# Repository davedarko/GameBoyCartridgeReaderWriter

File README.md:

# GameBoyCartridgeReaderWriter

it's currently a bit unsorted, but here you can find some more information on this project https://hackaday.io/project/16188/

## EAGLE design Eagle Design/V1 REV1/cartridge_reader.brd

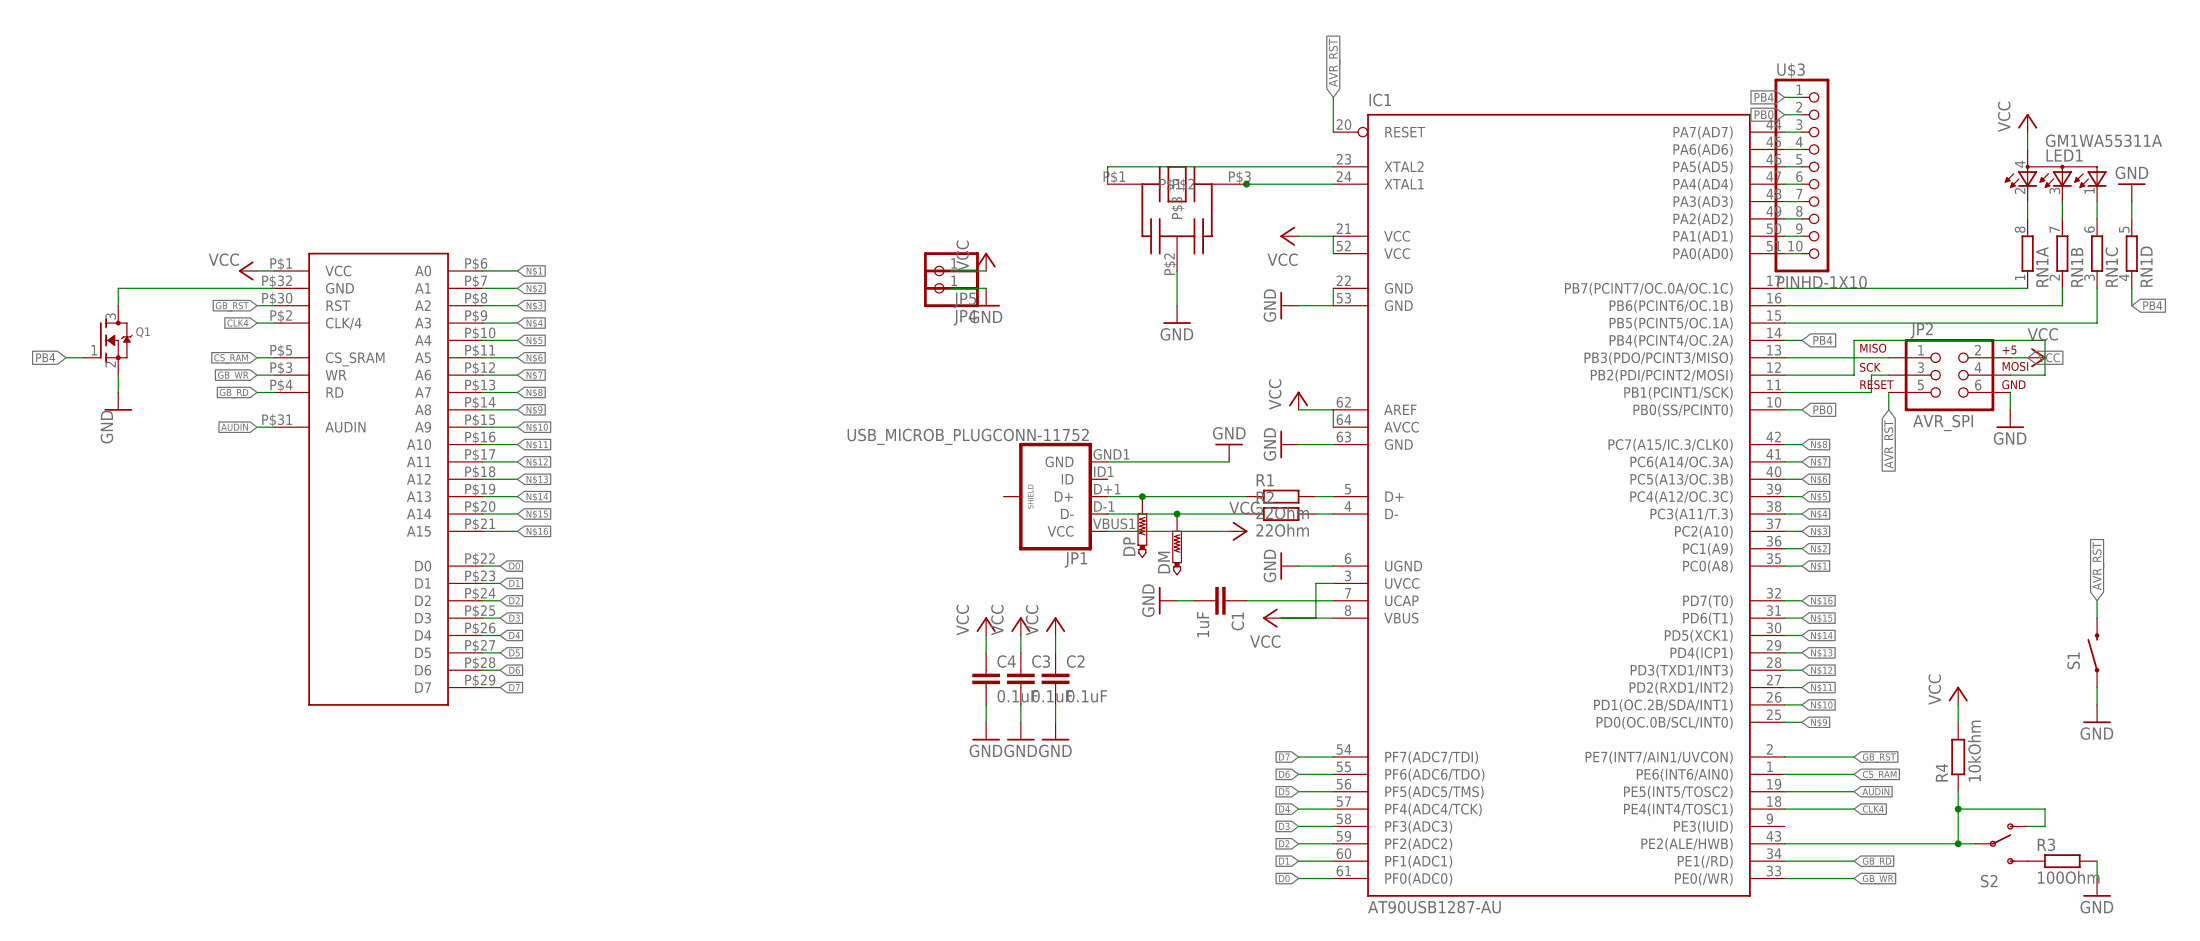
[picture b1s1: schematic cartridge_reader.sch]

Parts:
C1: 1uF; C0805K
C2, C3, C4: 0.1uF; C0805K
DM: PTR1TP18R; TP18R
DP: PTR1TP18R; TP18R
IC1: AT90USB1287-AU; TQFP64
JP1: USB_MICROB_PLUGCONN-11752; USB-B-MICRO-SMD_V03
JP2: AVR_SPI; 2X3_LOCK
JP4, JP5: PINHD-1X1; 1X01
LED1: GM1WA55311A
Q1: MOSFET-NREFLOW; SOT23
R1, R2: 22Ohm; R0603
R3: 100Ohm; R0603
R4: 10kOhm; R0603
RN1: 4R-N0603-ARC; 0603-ARC
S1: SWITCH-MOMENTARY-2-SMD-1101NE; TACTILE-SWITCH-1101NE
S2: SWITCH-SPDT-SMD-A; SWITCH-SPST-SMD-A
U$1: GMB_SOCKET; GAMEBOY_SOCKET
U$2: CSTCE
U$3: PINHD-1X10; 1X10-BIG

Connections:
AUDIN: IC1.19 (PE5(INT5/TOSC2)), U$1.P$31 (AUDIN)
AVR_RST: IC1.20 (RESET), JP2.5, S1.P$2 (2)
CLK4: IC1.18 (PE4(INT4/TOSC1)), U$1.P$2 (CLK/4)
CS_RAM: IC1.1 (PE6(INT6/AIN0)), U$1.P$5 (CS_SRAM)
D0: IC1.61 (PF0(ADC0)), U$1.P$22 (D0)
D1: IC1.60 (PF1(ADC1)), U$1.P$23 (D1)
D2: IC1.59 (PF2(ADC2)), U$1.P$24 (D2)
D3: IC1.58 (PF3(ADC3)), U$1.P$25 (D3)
D4: IC1.57 (PF4(ADC4/TCK)), U$1.P$26 (D4)
D5: IC1.56 (PF5(ADC5/TMS)), U$1.P$27 (D5)
D6: IC1.55 (PF6(ADC6/TDO)), U$1.P$28 (D6)
D7: IC1.54 (PF7(ADC7/TDI)), U$1.P$29 (D7)
GB_RD: IC1.34 (PE1(/RD)), U$1.P$4 (RD)
GB_RST: IC1.2 (PE7(INT7/AIN1/UVCON)), U$1.P$30 (RST)
GB_WR: IC1.33 (PE0(/WR)), U$1.P$3 (WR)
GND: C1.2, C2.2, C3.2, C4.2, IC1.6 (UGND), IC1.22 (GND), IC1.53 (GND), IC1.63 (GND), JP1.GND1 (GND), JP2.6, JP4.1, Q1.2 (S), R3.2, RN1.5 (2), S1.P$1 (1), U$2.P$2
unnamed: IC1.35 (PC0(A8)), U$1.P$6 (A0)
unnamed: IC1.36 (PC1(A9)), U$1.P$7 (A1)
unnamed: IC1.37 (PC2(A10)), U$1.P$8 (A2)
unnamed: IC1.38 (PC3(A11/T.3)), U$1.P$9 (A3)
unnamed: IC1.39 (PC4(A12/OC.3C)), U$1.P$10 (A4)
unnamed: IC1.40 (PC5(A13/OC.3B)), U$1.P$11 (A5)
unnamed: IC1.41 (PC6(A14/OC.3A)), U$1.P$12 (A6)
unnamed: IC1.42 (PC7(A15/IC.3/CLK0)), U$1.P$13 (A7)
unnamed: IC1.25 (PD0(OC.0B/SCL/INT0)), U$1.P$14 (A8)
unnamed: IC1.26 (PD1(OC.2B/SDA/INT1)), U$1.P$15 (A9)
unnamed: IC1.27 (PD2(RXD1/INT2)), U$1.P$16 (A10)
unnamed: IC1.28 (PD3(TXD1/INT3)), U$1.P$17 (A11)
unnamed: IC1.29 (PD4(ICP1)), U$1.P$18 (A12)
unnamed: IC1.30 (PD5(XCK1)), U$1.P$19 (A13)
unnamed: IC1.31 (PD6(T1)), U$1.P$20 (A14)
unnamed: IC1.32 (PD7(T0)), U$1.P$21 (A15)
unnamed: IC1.23 (XTAL2), U$2.P$1
unnamed: IC1.24 (XTAL1), U$2.P$3
unnamed: IC1.13 (PB3(PDO/PCINT3/MISO)), JP2.1
unnamed: IC1.12 (PB2(PDI/PCINT2/MOSI)), JP2.4
unnamed: DP.TP, JP1.D+1 (D+), R1.1
unnamed: DM.TP, JP1.D-1 (D-), R2.1
unnamed: IC1.5 (D+), R1.2
unnamed: IC1.4 (D-), R2.2
unnamed: IC1.11 (PB1(PCINT1/SCK)), JP2.3
unnamed: IC1.43 (PE2(ALE/HWB)), R4.1, S2.1 (O), S2.2
unnamed: C1.1, IC1.7 (UCAP)
unnamed: IC1.17 (PB7(PCINT7/OC.0A/OC.1C)), RN1.1
unnamed: IC1.16 (PB6(PCINT6/OC.1B)), RN1.2 (1)
unnamed: LED1.2 (CRED), RN1.8 (2)
unnamed: LED1.3 (CBLUE), RN1.7 (2)
unnamed: LED1.1 (CGREEN), RN1.6 (2)
unnamed: IC1.15 (PB5(PCINT5/OC.1A)), RN1.3 (1)
unnamed: IC1.44 (PA7(AD7)), U$3.3
unnamed: IC1.45 (PA6(AD6)), U$3.4
unnamed: IC1.46 (PA5(AD5)), U$3.5
unnamed: IC1.47 (PA4(AD4)), U$3.6
unnamed: IC1.48 (PA3(AD3)), U$3.7
unnamed: IC1.49 (PA2(AD2)), U$3.8
unnamed: IC1.50 (PA1(AD1)), U$3.9
unnamed: IC1.51 (PA0(AD0)), U$3.10
unnamed: Q1.3 (D), U$1.P$32 (GND)
unnamed: R3.1, S2.3 (S)
PB0: IC1.10 (PB0(SS/PCINT0)), U$3.2
PB4: IC1.14 (PB4(PCINT4/OC.2A)), Q1.1 (G), RN1.4 (1), U$3.1
VCC: C2.1, C3.1, C4.1, IC1.3 (UVCC), IC1.8 (VBUS), IC1.21 (VCC), IC1.52 (VCC), IC1.62 (AREF), IC1.64 (AVCC), JP1.VBUS1 (VCC), JP2.2, JP5.1, LED1.4 (A), R4.2, U$1.P$1 (VCC)

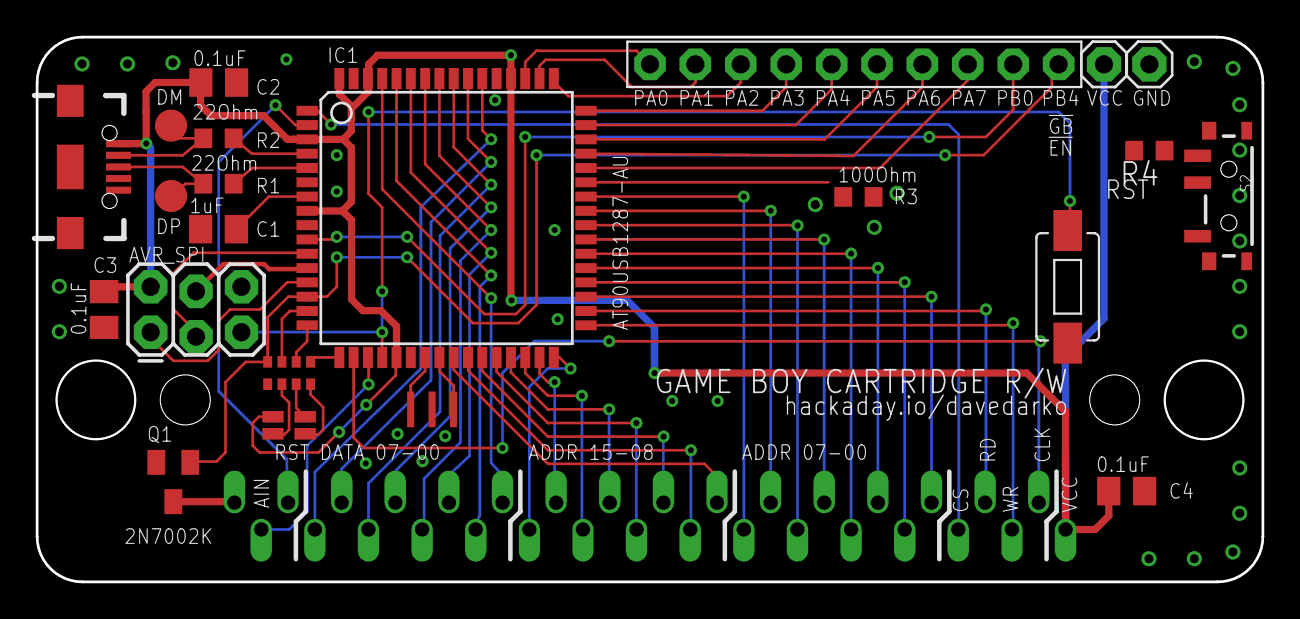
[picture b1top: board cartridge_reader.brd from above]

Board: 2 copper layers, 68.6 x 30.5 mm, 23 parts (1 on the bottom side), 62 nets.

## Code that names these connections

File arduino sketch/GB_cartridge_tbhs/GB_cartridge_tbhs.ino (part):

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// PORTD higher OUT
// PORTF DATA
// GB_RD E1
// GB_WR E0 // also called mreqPin in insideGadgets Version
// GB_RST E7

#define start_switch 19 // B0 lila
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#define led_blue 24 // B5
#define led_red 25 // B6
#define led_green 26 // B7
#define GB_WR 0 //E0
#define GB_RD 1 //E1
#define GB_RST 27 //E7
#define CS_SRAM 18 //E6
#define GB_AUD 47 //E5


#define wrPin_high    PORTE |= (1<<PE0);
#define wrPin_low     PORTE &= ~(1<<PE0);
#define rdPin_high    PORTE |= (1<<PE1);
#define rdPin_low     PORTE &= ~(1<<PE1);
#define GB_AUD_high  PORTE |= (1<<PE5);
#define GB_AUD_low   PORTE &= ~(1<<PE5);
#define mreqPin_high  PORTE |= (1<<PE6);
#define mreqPin_low   PORTE &= ~(1<<PE6);
#define reset_high  PORTE |= (1<<PE7);
#define reset_low   PORTE &= ~(1<<PE7);

long start_time = 0;
long restartTIME = 0;
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  digitalWrite(led_red, HIGH);
  digitalWrite(led_green, HIGH);

  pinMode(GB_WR, OUTPUT);
  pinMode(GB_RD, OUTPUT);
  pinMode(CS_SRAM, OUTPUT);
  pinMode(GB_RST, OUTPUT);
  pinMode(GB_AUD, OUTPUT);


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
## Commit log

2018-03-10 eagle design files
2018-03-22 lufa and cartridge dumper
2018-03-31 stuff

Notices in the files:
parts and their libraries:
SparkFun-Connectors: Licensing: Creative Commons ShareAlike 4.0 International - https://creativecommons.org/licenses/by-sa/4.0
